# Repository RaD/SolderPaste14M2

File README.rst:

This is a clone of `Solder Paste Controller`__ project from Dead Bug Prototypes.

__ https://www.tindie.com/products/Dead_Bug_Prototypes/solder-paste-controller/

The main differences are:

- Usage ATtiny13 as a MCU.
- Firmware is written with assembler language.

Flashing:

    sudo \
    avrdude -p attiny13 \
            -c usbasp \
            -P usb
            -U lfuse:w:0x6A:m -U hfuse:w:0xFF:m
            -U flash:w:solderpaste.hex

Fuse online editor: http://www.engbedded.com/fusecalc/

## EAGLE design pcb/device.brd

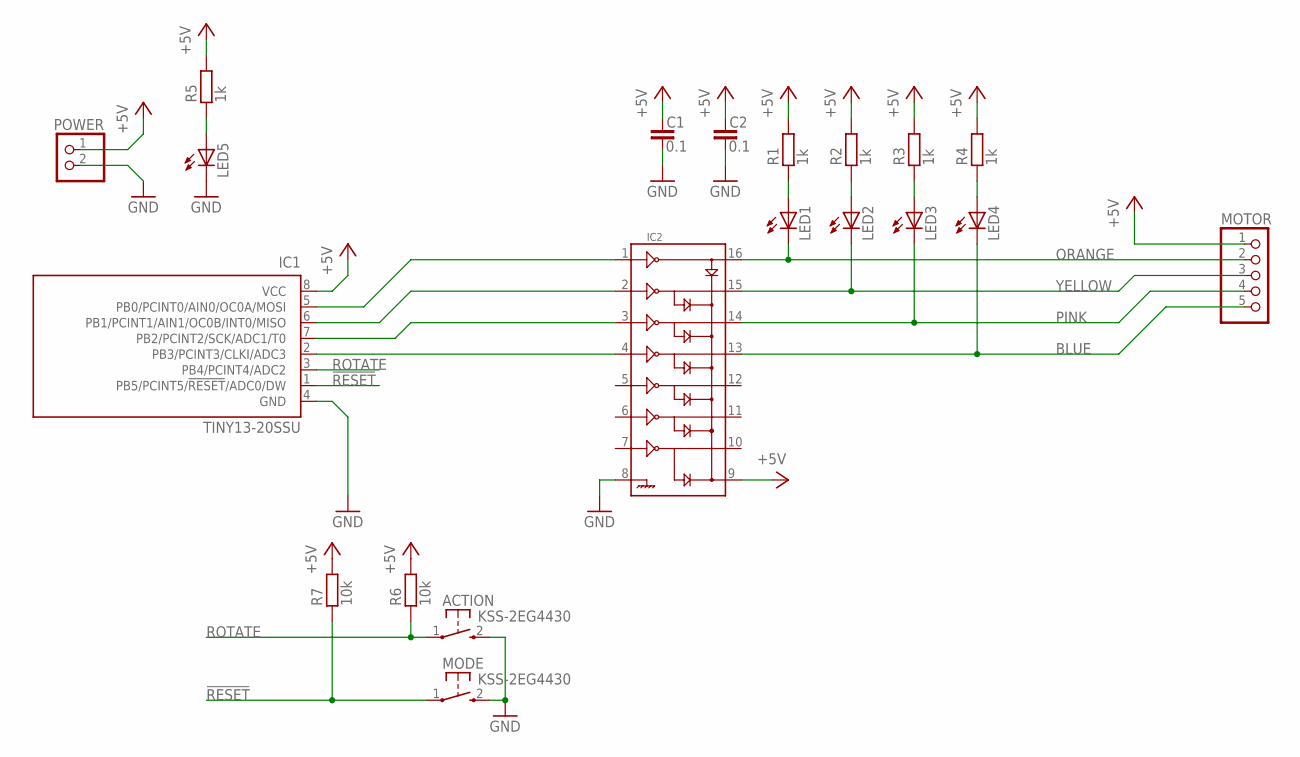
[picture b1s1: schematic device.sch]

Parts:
ACTION: KSS-2EG4430
C1, C2: 0.1; C0805
IC1: TINY13-20SSU; 8S1
IC2: ULN2003D; SO16
LED1, LED2, LED3, LED4, LED5: LEDCHIPLED_0805; CHIPLED_0805
MODE: KSS-2EG4430
MOTOR: PINHD-1X5_2.54; 1X05
POWER: PINHD-1X2_2.54; 1X02
R1, R2, R3, R4, R5: 1k; R0805
R6, R7: 10k; R0805

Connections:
!RESET: IC1.1 (PB5/PCINT5/!RESET!/ADC0/DW), MODE.1, R7.1
+5V: C1.1, C2.1, IC1.8 (VCC), IC2.9, MOTOR.1, POWER.1, R1.2, R2.2, R3.2, R4.2, R5.2, R6.2, R7.2
BLUE: IC2.13, LED4.C, MOTOR.5
GND: ACTION.2 (S), C1.2, C2.2, IC1.4 (GND), IC2.8, LED5.C, MODE.2 (S), POWER.2
unnamed: LED1.A, R1.1
unnamed: LED2.A, R2.1
unnamed: LED3.A, R3.1
unnamed: LED4.A, R4.1
unnamed: LED5.A, R5.1
unnamed: IC1.5 (PB0/PCINT0/AIN0/OC0A/MOSI), IC2.1
unnamed: IC1.6 (PB1/PCINT1/AIN1/OC0B/INT0/MISO), IC2.2
unnamed: IC1.7 (PB2/PCINT2/SCK/ADC1/T0), IC2.3
unnamed: IC1.2 (PB3/PCINT3/CLKI/ADC3), IC2.4
ORANGE: IC2.16, LED1.C, MOTOR.2
PINK: IC2.14, LED3.C, MOTOR.4
ROTATE: ACTION.1, IC1.3 (PB4/PCINT4/ADC2), R6.1
YELLOW: IC2.15, LED2.C, MOTOR.3

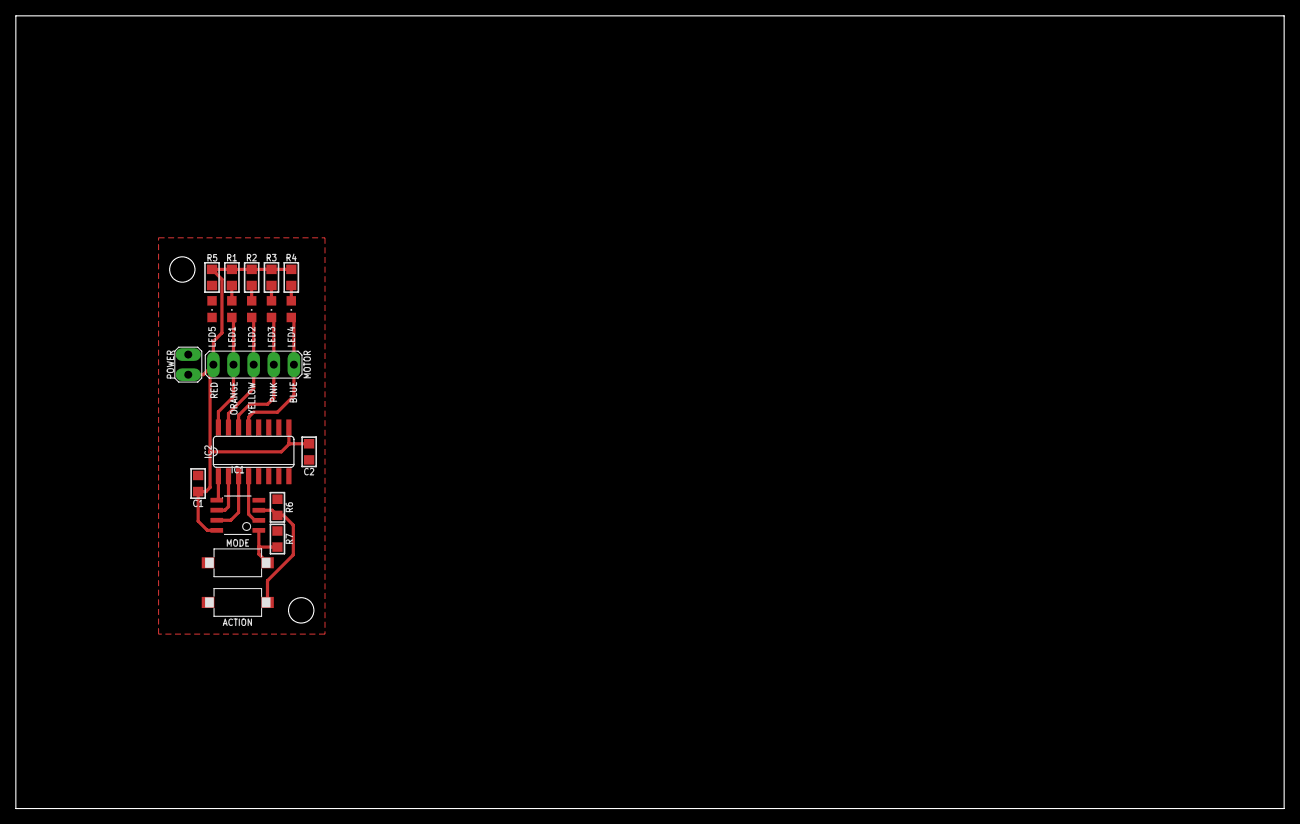
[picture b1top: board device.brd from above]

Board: 2 copper layers, 160.0 x 100.0 mm, 20 parts (0 on the bottom side), 17 nets.

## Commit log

2014-08-28 Keep the original code.
2014-08-28 Description of the project.
2014-08-28 A first glance on the firmware.
2014-08-28 A first glance on the PCB.
2014-08-28 Add Pin Change interrupt and fix switch mode part.
2014-08-29 Change the algorithm.
2014-08-29 Byte economy :)
2014-08-29 Delay.
2014-08-29 Use macros.
2014-08-31 Motor datasheet.
2014-08-31 Schematic for fast viewers.
2014-08-31 More info about.
2014-08-31 Fix motor connection and add pullup on action pin.
2014-08-31 Make motor rotating.
2014-08-31 Fix TABs.
2014-12-01 Small change of RESET detection code.
2014-12-03 Fix asm code.
2014-12-03 Move ASM to FIRMWARE/.
2014-12-03 Ready to use firmware.
2014-12-03 Almost ready PCB.
2014-12-03 Original STL.

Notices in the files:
parts and their libraries:
rc-master-smd: Copyright (C) 2007, Bob Starr
